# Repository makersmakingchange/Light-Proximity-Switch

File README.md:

# Light Proximity Switch

> [!IMPORTANT]
2026-Jan-16 Several of the electronic components in this design are no longer available. We are working to determine suitable replacements.

The Light Proximity Switch is an open-source assistive switch that is activated by movement or extremely light contact. It can be activated by waving a hand or limb over the device. This switch has an output cable with a standard 3.5 mm plug and it can be used to control a variety of switch-adapted devices including phones, computers, adapted toys, and gaming consoles.

The Light Proximity Switch is comprised of off-the-shelf electronics, a custom printed circuit board (PCB), and 3D printed parts.

The Light Proximity Switch is open assistive technology (OpenAT). Under the terms of the open source licenses, the device may be built, used, and improved by anyone.

The overall cost of materials for a single build is approximately $35 CAD.

## More info at

- [Makers Making Change Library Page](https://www.makersmakingchange.com/s/product/light-proximity-switch/01tJR0000006942YAA)

## Usage
Plug the 3.5 mm cable from the switch into the device you want to control. Wave a hand or limb over the sensor to trigger the device (the green LED should light up). 

Fine tune the motion sensitivity by toggling the black switch to "HI" or "LO" then fine tuning using the blue dial.

To attach the 3D printed circular base, simply slide the base onto the switch until it clicks into place. This may take a bit of force. The inclined surface of the can make it easier for a user to push their hand up to activate the sensor.

## How to Obtain the Device
### 1. Do-it-Yourself (DIY) or Do-it-Together (DIT)

This is an open-source assistive technology, so anyone is free to build it. All of the files and instructions required to build the device are contained within this repository. Refer to the documentation below.

### 2. Request a build of this device

You may also submit a build request through the [MMC Library Page](https://www.makersmakingchange.com/s/product/light-proximity-switch/01tJR0000006942YAA) to have a volunteer maker build the device. As the requestor, you are responsible for reimbursing the maker for the cost of materials and any shipping.

### 3. Build this device for someone else

If you have the skills and equipment to build this device, and would like to donate your time to create the device for someone who needs it, visit the [MMC Maker Wanted](https://makersmakingchange.com/maker-wanted/) section.

## Build Instructions

### 1. Read through the Documentation

<!--- The [Assembly Guide](/Documentation/Light_Proxity_Switch_Makery_Guide.pdf) contains all the necessary information to build this device, including tool lists, assembly instructions, and testing. --->
Read through the documentation below.

### 2. Order the Custom Printed Circuit Board (PCB)

This device requires a custom PCB. It will need to be ordered from a PCB fabrication service. The Gerber files can be found in the [PCB Build Files](/Build_Files/PCB_Build_Files/). 

### 3. Order the Off-The-Shelf Components

The [Bill of Materials](/Documentation/Light_Proximity_Switch_BOM.csv) lists all of the parts and components required to build the device. This build also requires a custom PCB.

### 4. Print the 3D Printable components

All of the individual print files can be found in the [/Build_Files/3D_Printing_Files](/Build_Files/3D_Printing_Files/) folder.

### 5. Assemble the Light Proximity Switch

Reference the [Assembly Guide](/Documentation/Light_Proxity_Switch_Assembly_Guide.pdf) for the tools and steps required to build each portion.

## How to improve this Device Design
As open assistive technology, you are welcomed and encouraged to improve upon the design. 

## Files
### Documentation
| Document             | Version | Link |
|----------------------|---------|------|
| Design Rationale     | n/a     | WIP   |
| Bill of Materials    | 1.0     |  [Light Proximity Switch BOM](/Documentation/Light_Proximity_Switch_BOM.csv)  |
| Tool List | 1.0 | [Light Proximity Switch Tools List](/Documentation/Light_Proximity_Switch_Tools_List.pdf)|
| Assembly Guide       | 1.0     | [Light Proximity Switch Assembly Guide](/Documentation/Light_Proxity_Switch_Assembly_Guide.pdf) |
| QC Quide | 1.0 | [Light Proximity Switch QC Guide](/Documentation/Light_Proximity_Switch_QC_Guide.pdf)|
| Troubleshooting Guide | 1.0 | [Light Proximity Switch Troubleshooting Guide](/Documentation/Light_Proximity_Switch_Troubleshooting_Guide.pdf)|
| Delivery Checklist | 1.0 | [Light Proximity Delivery Checklist](/Documentation/Light_Proximity_Switch_Delivery_Checklist.pdf)|
| User Guide           | 1.0     | [Light Proximity Switch User Guide](/Documentation/Light_Proximity_Switch_User_Guide.pdf) |
| Changelog            | n/a     | -     |

### Design Files
<!---
DESIGN FILES
--->
 - [CAD Files](/Design_Files/CAD_Design_Files)
 - [PCB Design Files](/Design_Files/PCB_Design_Files/)

### Build Files
 - [3D Printing Files](/Build_Files/3D_Printing_Files)
 - [PCB Build Files](/Build_Files/PCB_Build_Files)

## License
Copyright (c) 2019-2026 Neil Squire / Makers Making Change.

This repository describes Open Hardware:
 - Everything needed or used to design, make, test, or prepare the Light Proximity Switch is licensed under the [CERN 2.0 Weakly Reciprocal license (CERN-OHL-W v2) or later](https://cern.ch/cern-ohl ) .
 - Accompanying material such as instruction manuals, videos, and other copyrightable works that are useful but not necessary to design, make, test, or prepare the Light Proximity Switch are published under a [Creative Commons Attribution-ShareAlike 4.0 license (CC BY-SA 4.0)](https://creativecommons.org/licenses/by-sa/4.0/) .

You may redistribute and modify this documentation and make products using it under the terms of the [CERN-OHL-W v2](https://cern.ch/cern-ohl).
This documentation is distributed WITHOUT ANY EXPRESS OR IMPLIED WARRANTY, INCLUDING OF MERCHANTABILITY, SATISFACTORY QUALITY AND FITNESS FOR A PARTICULAR PURPOSE.
Please see the CERN-OHL-W v2 for applicable conditions.

Source Location: https://github.com/makersmakingchange/Light-Proximity-Switch

## Attribution
The Light Proximity Switch is an original design by Neil Squire / Maker Making Change Program.

### Contributors
  - Derrick Andrews, Neil Squire Society / Makers Making Change.
  - Jake McIvor, Neil Squire Society / Makers Making Change.
  - Kristina Mok, Neil Squire Society / Makers Making Change.

<!-- ABOUT MMC START -->
## About Makers Making Change

Makers Making Change is a program of [Neil Squire](https://www.neilsquire.ca/), a Canadian non-profit that uses technology, knowledge, and passion to empower people with disabilities.

Makers Making Change leverages the capacity of community based Makers, Disability Professionals and Volunteers to develop and deliver affordable Open Source Assistive Technologies.

 - Website: [www.MakersMakingChange.com](https://www.makersmakingchange.com/)
 - GitHub: [makersmakingchange](https://github.com/makersmakingchange)
 - Bluesky: [@makersmakingchange.bsky.social](https://bsky.app/profile/makersmakingchange.bsky.social)
 - Instagram: [@makersmakingchange](https://www.instagram.com/makersmakingchange)
 - Facebook: [makersmakechange](https://www.facebook.com/makersmakechange)
 - LinkedIn: [Neil Squire Society](https://www.linkedin.com/company/neil-squire-society/)
 - Thingiverse: [makersmakingchange](https://www.thingiverse.com/makersmakingchange/about)
 - Printables: [MakersMakingChange](https://www.printables.com/@MakersMakingChange)

### Contact Us
For technical questions, to get involved, or to share your experience we encourage you to [visit our website](https://www.makersmakingchange.com/) or [contact us](https://www.makersmakingchange.com/s/contact).
<!-- ABOUT MMC END -->

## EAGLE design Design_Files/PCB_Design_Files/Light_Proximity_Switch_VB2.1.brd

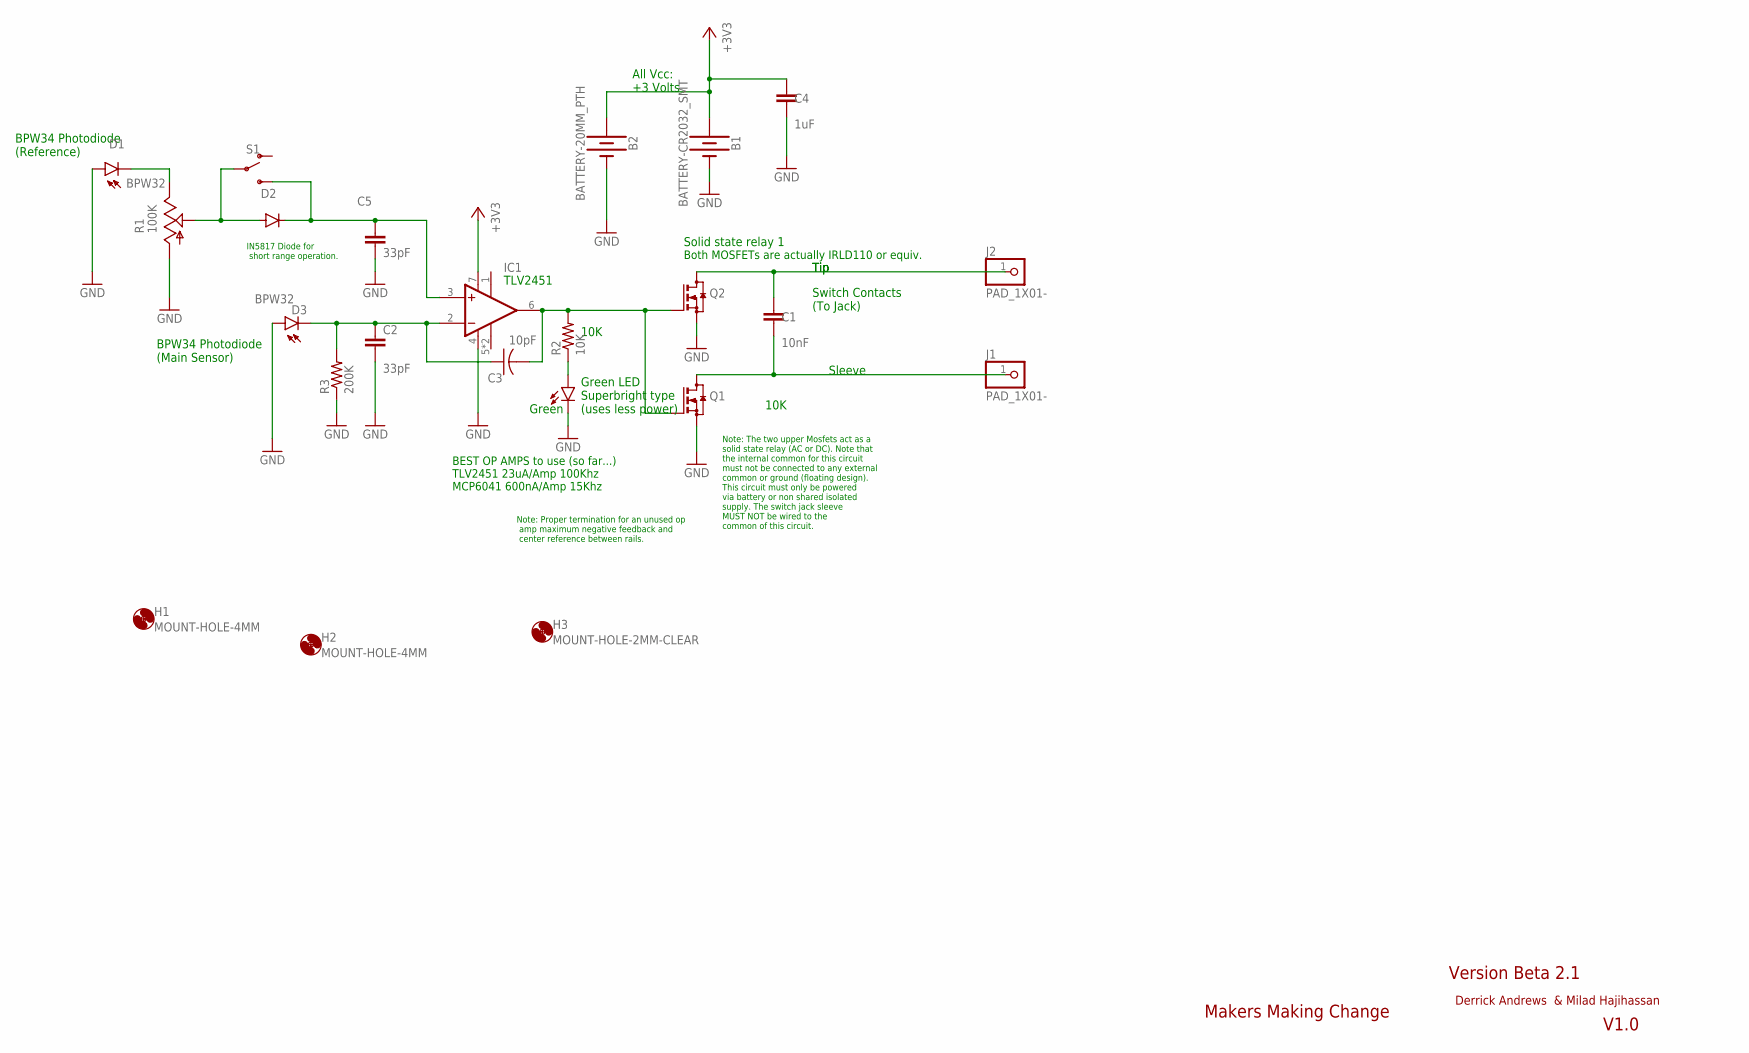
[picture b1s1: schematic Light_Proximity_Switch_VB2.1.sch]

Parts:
B1: BATTERY-CR2032_SMT; CR2032_SMT_HOLDER
B2: BATTERY-20MM_PTH; BATTCOM_20MM_PTH
C1: 10nF; CAP-PTH-SMALL-KIT
C2, C5: 33pF; CAP-PTH-SMALL-KIT
C3: 10pF; C025-030X050
C4: 1uF; CAP-PTH-SMALL-KIT
D1, D3: BPW32
D2: DIODE-DO41; DO41-10
H1, H2: MOUNT-HOLE-4MM; HOLE-4MM
H3: MOUNT-HOLE-2MM-CLEAR; HOLE-2MM-CLEAR
IC1: TLV2451; DIL08
J1, J2: PAD_1X01-; PAD-1X01
LED1: LED_5MM-5MM-GREEN; LED_5MM_GREEN
Q1, Q2: IRLD110-HVM-DIP; HVM-DIP
R1: 100K; 3386P-T
R2: 10K; RESISTOR_0206/8
R3: 200K; RESISTOR_0206/8
S1: SWITCH-SPDT-PTH_11.6X4.0MM; SWITCH_SPDT_PTH_11.6X4.0MM

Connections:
+3V3: B1.+, B2.+, C4.1, IC1.7 (V+)
GND: B1.-, B2.-, C2.2, C4.2, C5.2, D1.A, D3.A, IC1.4 (V-), LED1.K (C), Q1.2 (S), Q2.2 (S), R1.A, R3.1
unnamed: D2.A, R1.S, S1.2
unnamed: C5.1, D2.C, IC1.3 (+IN), S1.3 (S)
unnamed: D1.K (C), R1.E
unnamed: C3.2, IC1.6 (OUT), Q1.1 (G), Q2.1 (G), R2.2
unnamed: C1.2, J1.1, Q1.3 (D)
unnamed: C1.1, J2.1, Q2.3 (D)
unnamed: C2.1, C3.1, D3.K (C), IC1.2 (-IN), R3.2
unnamed: LED1.A, R2.1

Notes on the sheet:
Makers Making Change
V1.0
Derrick Andrews & Milad Hajihassan
All Vcc: +3 Volts
Switch Contacts (To Jack)
10K
Note: The two upper Mosfets act as a solid state relay (AC or DC). Note that the internal common for this circuit must not be connected to any external common or ground (floating design). This circuit must only be powered via battery or non shared isolated supply. The switch jack sleeve MUST NOT be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
Tip
Sleeve
Solid state relay 1
Green LED Superbright type (uses less power)
Green
BEST OP AMPS to use (so far...) TLV2451 23uA/Amp 100Khz MCP6041 600nA/Amp 15Khz
BPW34 Photodiode (Main Sensor)
BPW34 Photodiode (Reference)
Note: Proper termination for an unused op amp maximum negative feedback and center reference between rails.
Both MOSFETs are actually IRLD110 or equiv.
IN5817 Diode for short range operation.
TLV2451
Version Beta 2.1

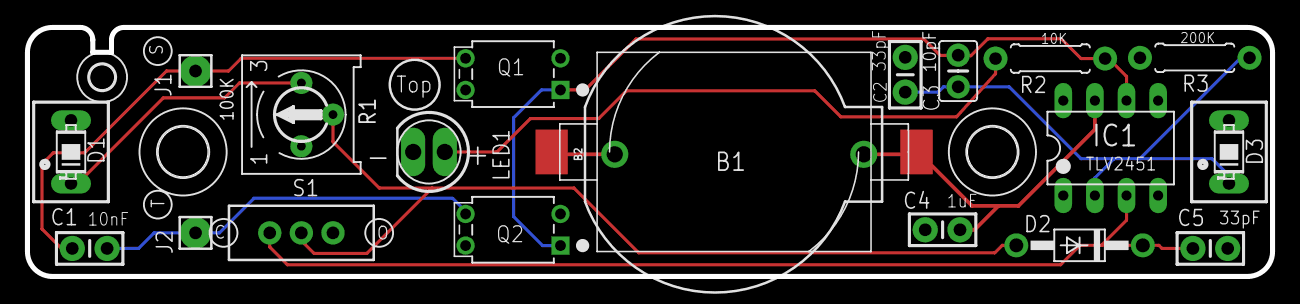
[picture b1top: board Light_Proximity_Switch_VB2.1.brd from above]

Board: 2 copper layers, 100.0 x 20.0 mm, 23 parts (0 on the bottom side), 10 nets.

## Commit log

2020-05-06 Update Light_Proximity_Switch_Base_v1.0.stl
    Correct default orientation.
2020-05-06 Update 3D Print info
    Add 3d printing settings and orientation photo
2020-05-07 Correct folder naming
2020-05-07 Correct folder naming Pt 2
2020-05-08 Added the PCB Fabrication Manual
2020-05-13 Added gerber files and board/schematics pdf files.
2020-05-13 Added MMC PCB Fabrication Manual document.
2020-09-16 Update Forum link
2021-04-01 Added PCBWay gerbers
2021-07-02 Create Light_Proximity_Switch_BOM_v1.0.md
    Add markdown version of BOM
2021-07-02 Add Assembly Guide version
2021-07-02 Delete Light_Proximity_Switch_Delivery_Checklist.pdf
    Remove duplicate
2021-07-02 Standardize User Guide filename
2025-04-04 Update to bottom case and renaming
    - Updated the bottom case model so improve printing of the unsupported screw holes.
    - Renamed stl files to remove versioning to make consistent with newer libraries
    - Added .STEP files in Design_Files folder
2025-04-08 Update About MMC Section
2025-04-10 Add Update About MMC GitHub Action
2026-01-17 Update and expand license documentation
2026-01-17 Add images for light proximity switch project
    Added three new image files: Light_Proximity_Usage.gif, Light_Proximity_Switch.jpg, and Light_Proximity_switch_Base.gif to the Photos directory
2026-01-17 Rename and reorganize documentation
2026-01-17 Rename 3D printing file folder to match OpenAT Template
    3D_Printing -> 3D_Printing_Files
2026-01-17 Reorganize PCB files
2026-01-17 Reogranize CAD files
2026-01-17 Update Light Proximity Switch BOM components and pricing
    Revised the Bill of Materials for the Light Proximity Switch to update suppliers, manufacturers, part numbers, and pricing. Notable changes include switching the op-amp to MCP6231-E/P, updating sever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
2026-04-08 Updated Base File
    Added the correct base file as the previous one was a accidental copy of the bottom case. This is relevant to Issue: ""Base" file is wrong #11"

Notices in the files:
parts and their libraries:
SparkFun-Aesthetics: Licensing: Creative Commons ShareAlike 4.0 International - https://creativecommons.org/licenses/by-sa/4.0
